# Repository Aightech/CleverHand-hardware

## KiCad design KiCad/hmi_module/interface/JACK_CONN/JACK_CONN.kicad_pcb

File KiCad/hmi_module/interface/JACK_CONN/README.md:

# Communication Module
This module is responsible for handling the communication between the different modules of the master node.

The communication bus is composed of :
- Power supply (3.3V) and ground
- SPI bus (POCI, PICO, SCK)
- I2C bus (SDA, SCL)
- Address bus (A0, A1, A2, A3, A4)
- External reference voltage (AREF)

When the module is connected to the bus, it is assigned an address by the master node. This address is used to identify the module on the bus.
The communication module will will activate the chip select line of the associated sensor module when the address bus matches its address.
Additionally, each module has a unique identifier that is used to identify the module on the I2C bus.

## Electrical Schematic

## PCB Layout

## 3D Model

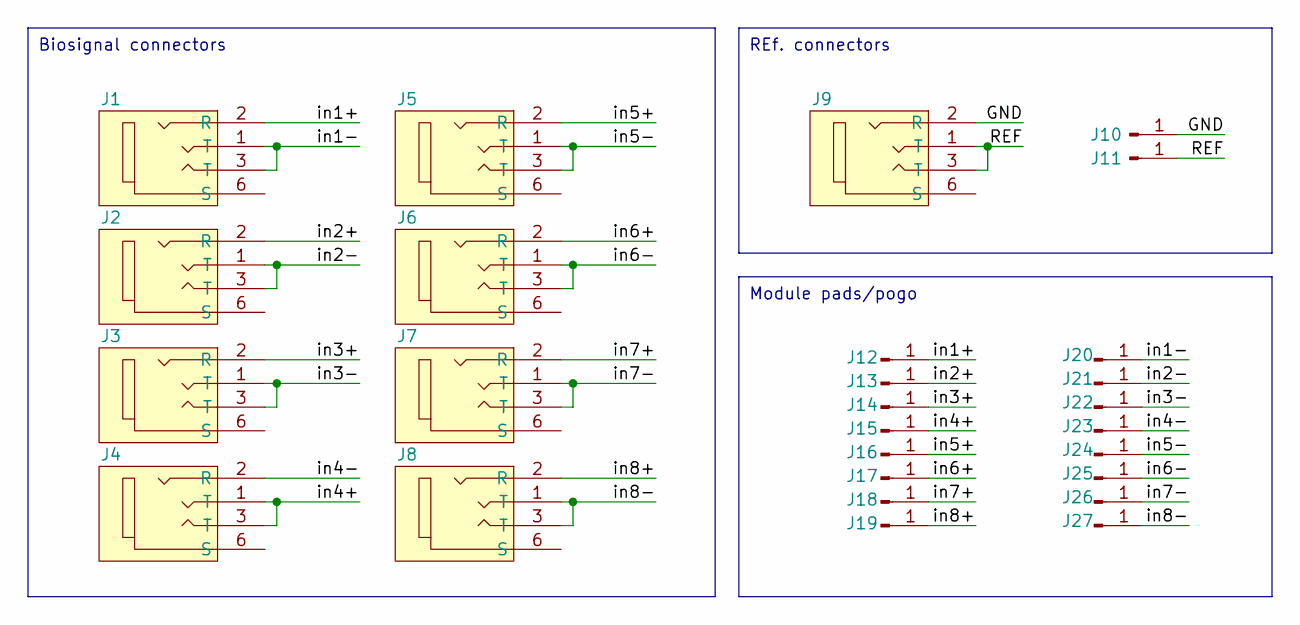
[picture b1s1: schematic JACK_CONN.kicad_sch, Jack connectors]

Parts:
J1, J2, J3, J4, J5, J6, J7, J8, J9: jack2.5_PJ-210B; Jack_Socket_PJ-210B
J10, J11: Conn_01x01_Pin; PinHeader_1x01_P2.54mm_Vertical
J12, J13, J14, J15, J16, J17, J18, J19, J20, J21, J22, J23, J24, J25, J26, J27: Conn_01x01_Pin; Pin_D1.2mm_pogo

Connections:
/GND: J9.2 (R), J10.1
/REF: J9.1 (T), J9.3 (T), J11.1
/in1+: J1.2 (R), J12.1
/in1-: J1.1 (T), J1.3 (T), J20.1
/in2+: J2.2 (R), J13.1
/in2-: J2.1 (T), J2.3 (T), J21.1
/in3+: J3.2 (R), J14.1
/in3-: J3.1 (T), J3.3 (T), J22.1
/in4+: J4.1 (T), J4.3 (T), J15.1
/in4-: J4.2 (R), J23.1
/in5+: J5.2 (R), J16.1
/in5-: J5.1 (T), J5.3 (T), J24.1
/in6+: J6.2 (R), J17.1
/in6-: J6.1 (T), J6.3 (T), J25.1
/in7+: J7.2 (R), J18.1
/in7-: J7.1 (T), J7.3 (T), J26.1
/in8+: J8.2 (R), J19.1
/in8-: J8.1 (T), J8.3 (T), J27.1

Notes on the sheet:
Module pads/pogo
Biosignal connectors
REf. connectors

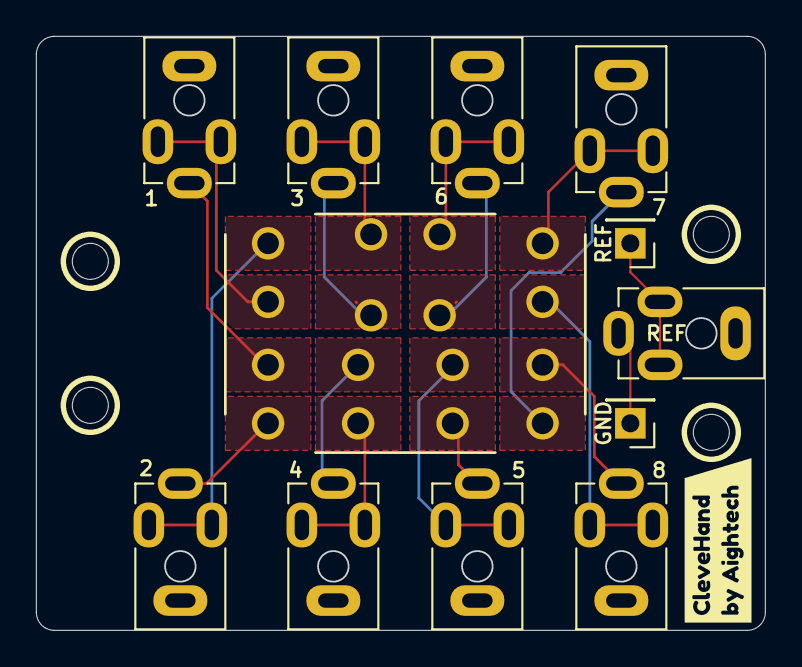
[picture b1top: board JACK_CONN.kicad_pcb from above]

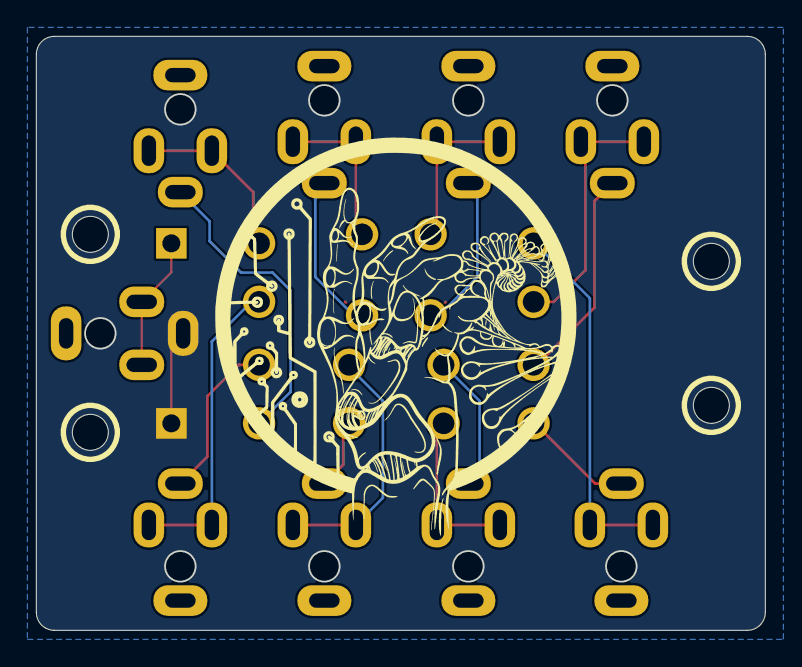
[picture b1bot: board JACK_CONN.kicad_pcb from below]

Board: 4 copper layers, 40.5 x 33.0 mm, 28 parts (16 on the bottom side), 18 nets.

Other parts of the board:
kibuzzard-6607178A: G***; kibuzzard-6607178A

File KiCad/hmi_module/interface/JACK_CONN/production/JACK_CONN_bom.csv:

"Reference","Value","Footprint","DNP","LCSC"
"J1","jack2.5_PJ-210B","00_custom-footprints:Jack_Socket_PJ-210B","",""
"J2","jack2.5_PJ-210B","00_custom-footprints:Jack_Socket_PJ-210B","",""
"J3","jack2.5_PJ-210B","00_custom-footprints:Jack_Socket_PJ-210B","",""
"J4","jack2.5_PJ-210B","00_custom-footprints:Jack_Socket_PJ-210B","",""
"J5","jack2.5_PJ-210B","00_custom-footprints:Jack_Socket_PJ-210B","",""
"J6","jack2.5_PJ-210B","00_custom-footprints:Jack_Socket_PJ-210B","",""
"J7","jack2.5_PJ-210B","00_custom-footprints:Jack_Socket_PJ-210B","",""
"J8","jack2.5_PJ-210B","00_custom-footprints:Jack_Socket_PJ-210B","",""
"J9","jack2.5_PJ-210B","00_custom-footprints:Jack_Socket_PJ-210B","",""
"J10","Conn_01x01_Pin","Connector_PinHeader_2.54mm:PinHeader_1x01_P2.54mm_Vertical","",""
"J11","Conn_01x01_Pin","Connector_PinHeader_2.54mm:PinHeader_1x01_P2.54mm_Vertical","",""
"J12","Conn_01x01_Pin","00_custom-footprints:Pin_D1.2mm_pogo","",""
"J13","Conn_01x01_Pin","00_custom-footprints:Pin_D1.2mm_pogo","",""
"J14","Conn_01x01_Pin","00_custom-footprints:Pin_D1.2mm_pogo","",""
"J15","Conn_01x01_Pin","00_custom-footprints:Pin_D1.2mm_pogo","",""
"J16","Conn_01x01_Pin","00_custom-footprints:Pin_D1.2mm_pogo","",""
"J17","Conn_01x01_Pin","00_custom-footprints:Pin_D1.2mm_pogo","",""
"J18","Conn_01x01_Pin","00_custom-footprints:Pin_D1.2mm_pogo","",""
"J19","Conn_01x01_Pin","00_custom-footprints:Pin_D1.2mm_pogo","",""
"J20","Conn_01x01_Pin","00_custom-footprints:Pin_D1.2mm_pogo","",""
"J21","Conn_01x01_Pin","00_custom-footprints:Pin_D1.2mm_pogo","",""
"J22","Conn_01x01_Pin","00_custom-footprints:Pin_D1.2mm_pogo","",""
"J23","Conn_01x01_Pin","00_custom-footprints:Pin_D1.2mm_pogo","",""
"J24","Conn_01x01_Pin","00_custom-footprints:Pin_D1.2mm_pogo","",""
"J25","Conn_01x01_Pin","00_custom-footprints:Pin_D1.2mm_pogo","",""
"J26","Conn_01x01_Pin","00_custom-footprints:Pin_D1.2mm_pogo","",""
"J27","Conn_01x01_Pin","00_custom-footprints:Pin_D1.2mm_pogo","",""

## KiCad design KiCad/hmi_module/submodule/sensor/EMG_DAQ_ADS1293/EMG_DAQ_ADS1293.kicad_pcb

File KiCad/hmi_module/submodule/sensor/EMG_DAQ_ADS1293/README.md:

# EMG ADS1293 Module
This module is a data acquisition module that embeds the ADS1293 analog front-end. It is responsible for acquiring the EMG signals from the electrodes.

## Electrical Schematic

## PCB Layout

## 3D Model

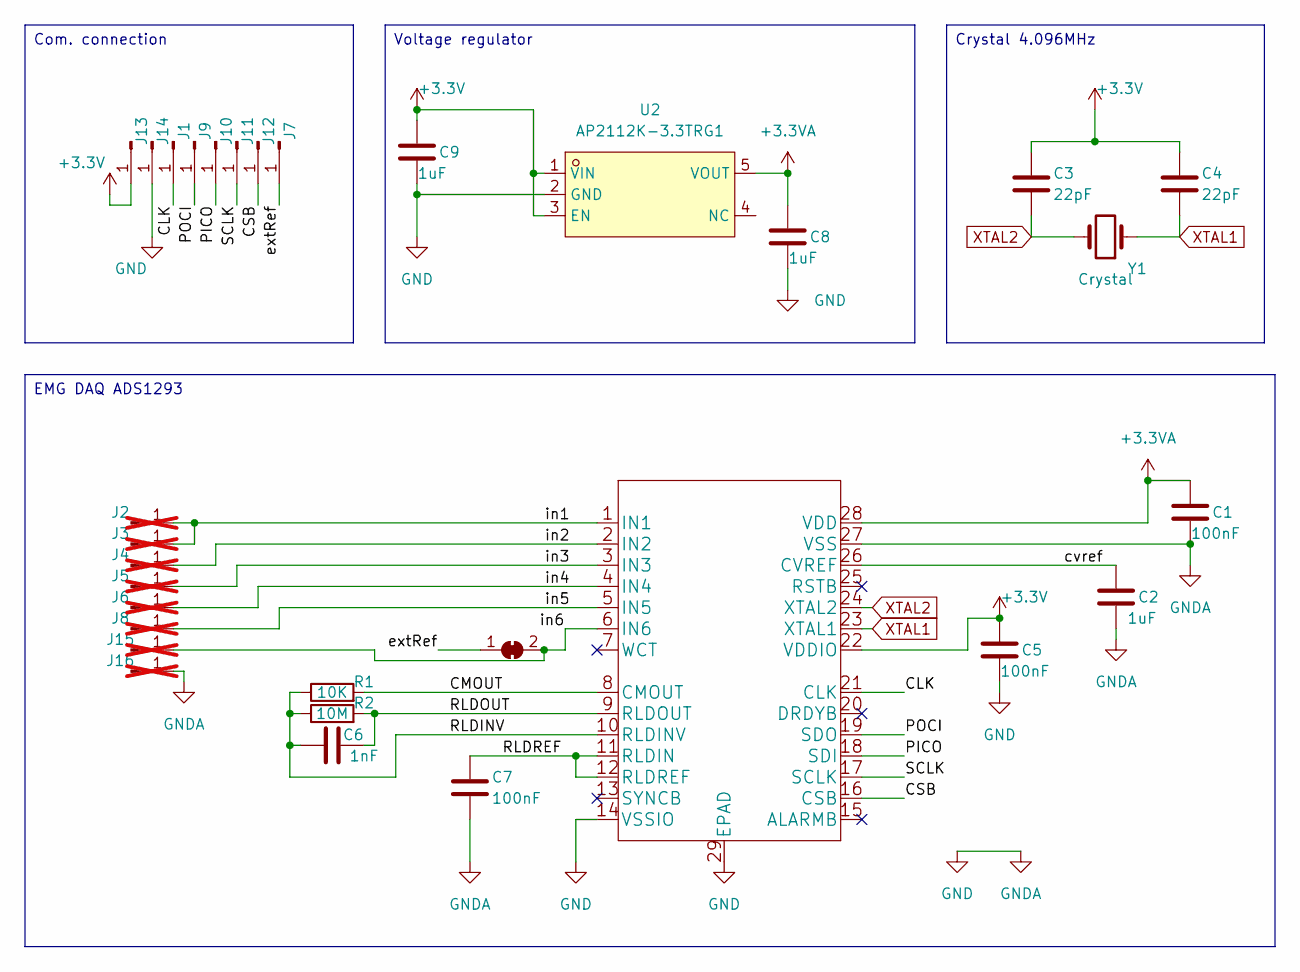
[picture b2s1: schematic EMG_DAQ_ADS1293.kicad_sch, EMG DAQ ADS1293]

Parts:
C1, C5, C7: 100nF; C_0402_1005Metric
C2, C8, C9: 1uF; C_0402_1005Metric
C3, C4: 22pF; C_0402_1005Metric
C6: 1nF; C_0402_1005Metric
J1, J7, J9, J10, J11, J12, J13, J14: Conn_01x01_Pin; PinHeader_1x01_P1.27mm_Vertical
J2, J3, J4, J5, J6, J8, J15, J16: Conn_01x01_Pin; PinHeader_1x01_P1.27mm_Vertical; not fitted
JP2: SolderJumper_2_Bridged; SolderJumper-2_P1.3mm_Bridged2Bar_RoundedPad1.0x1.5mm
R1: 10K; C_0402_1005Metric
R2: 10M; C_0402_1005Metric
U1: ADS1293CISQE-NOPB; ADS1293CISQE; LCSC C181260
U2: AP2112K-3.3TRG1; SOT-25-5_L2.9-W1.6-P0.95-LS2.8-BL; LCSC Part C51118
Y1: Crystal; Crystal_SMD_HC49-SD; LCSC C74858

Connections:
+3.3V: C3.1, C4.1, C5.1, C9.1, J13.1, U1.22 (VDDIO), U2.1 (VIN), U2.3 (EN)
+3.3VA: C1.1, C8.1, U1.28 (VDD), U2.5 (VOUT)
/CLK: J1.1, U1.21 (CLK)
/CMOUT: R1.2, U1.8 (CMOUT)
/CSB: J12.1, U1.16 (CSB)
/PICO: J10.1, U1.18 (SDI)
/POCI: J9.1, U1.19 (SDO)
/RLDINV: C6.1, R1.1, R2.1, U1.10 (RLDINV)
/RLDOUT: C6.2, R2.2, U1.9 (RLDOUT)
/RLDREF: C7.1, U1.11 (RLDIN), U1.12 (RLDREF)
/SCLK: J11.1, U1.17 (SCLK)
/cvref: C2.1, U1.26 (CVREF)
/extRef: J7.1, JP2.1 (A)
/in1: J2.1, J3.1, U1.1 (IN1)
/in2: J4.1, U1.2 (IN2)
/in3: J5.1, U1.3 (IN3)
/in4: J6.1, U1.4 (IN4)
/in5: J8.1, U1.5 (IN5)
/in6: J15.1, JP2.2 (B), U1.6 (IN6)
GND: C1.2, C2.2, C5.2, C7.2, C8.2, C9.2, J14.1, J16.1, U1.14 (VSSIO), U1.27 (VSS), U1.29 (EPAD), U2.2 (GND)
XTAL1: C4.2, U1.23 (XTAL1), Y1.1
XTAL2: C3.2, U1.24 (XTAL2), Y1.2

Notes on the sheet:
Com. connection
Crystal 4.096MHz
Voltage regulator
EMG DAQ ADS1293

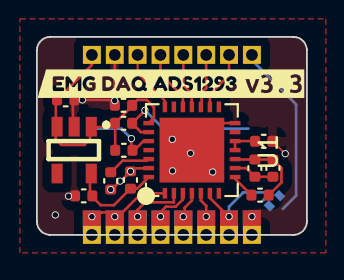
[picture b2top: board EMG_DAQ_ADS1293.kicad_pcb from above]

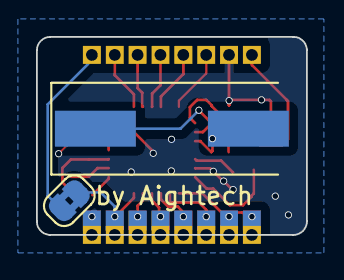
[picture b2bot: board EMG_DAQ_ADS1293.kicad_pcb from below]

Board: 4 copper layers, 15.0 x 11.0 mm, 33 parts (2 on the bottom side), 22 nets.

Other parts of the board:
kibuzzard-658D7E24: G***; kibuzzard-658D7E24
kibuzzard-69472C09: G***; kibuzzard-69472C09

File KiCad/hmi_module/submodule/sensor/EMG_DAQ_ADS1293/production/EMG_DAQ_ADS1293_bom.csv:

"Reference","Value","Footprint","DNP","LCSC"
"C1","100nF","Capacitor_SMD:C_0402_1005Metric","",""
"C2","1uF","Capacitor_SMD:C_0402_1005Metric","",""
"C3","22pF","Capacitor_SMD:C_0402_1005Metric","",""
"C4","22pF","Capacitor_SMD:C_0402_1005Metric","",""
"C5","100nF","Capacitor_SMD:C_0402_1005Metric","",""
"C6","1nF","Capacitor_SMD:C_0402_1005Metric","",""
"C7","100nF","Capacitor_SMD:C_0402_1005Metric","",""
"C8","1uF","Capacitor_SMD:C_0402_1005Metric","",""
"C9","1uF","Capacitor_SMD:C_0402_1005Metric","",""
"J1","Conn_01x01_Pin","Connector_PinHeader_1.27mm:PinHeader_1x01_P1.27mm_Vertical","",""
"J7","Conn_01x01_Pin","Connector_PinHeader_1.27mm:PinHeader_1x01_P1.27mm_Vertical","",""
"J9","Conn_01x01_Pin","Connector_PinHeader_1.27mm:PinHeader_1x01_P1.27mm_Vertical","",""
"J10","Conn_01x01_Pin","Connector_PinHeader_1.27mm:PinHeader_1x01_P1.27mm_Vertical","",""
"J11","Conn_01x01_Pin","Connector_PinHeader_1.27mm:PinHeader_1x01_P1.27mm_Vertical","",""
"J12","Conn_01x01_Pin","Connector_PinHeader_1.27mm:PinHeader_1x01_P1.27mm_Vertical","",""
"J13","Conn_01x01_Pin","Connector_PinHeader_1.27mm:PinHeader_1x01_P1.27mm_Vertical","",""
"J14","Conn_01x01_Pin","Connector_PinHeader_1.27mm:PinHeader_1x01_P1.27mm_Vertical","",""
"JP2","SolderJumper_2_Bridged","Jumper:SolderJumper-2_P1.3mm_Bridged2Bar_RoundedPad1.0x1.5mm","",""
"R1","10K","Capacitor_SMD:C_0402_1005Metric","",""
"R2","10M","Capacitor_SMD:C_0402_1005Metric","",""
"U1","ADS1293CISQE-NOPB","00_Custom:ADS1293CISQE","",""
"U2","AP2112K-3.3TRG1","00_lcsc:SOT-25-5_L2.9-W1.6-P0.95-LS2.8-BL","","C51118"
"Y1","Crystal","Crystal:Crystal_SMD_HC49-SD","",""

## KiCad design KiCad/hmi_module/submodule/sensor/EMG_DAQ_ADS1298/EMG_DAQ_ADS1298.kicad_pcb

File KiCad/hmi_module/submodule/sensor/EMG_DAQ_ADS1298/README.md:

# EMG ADS1298 Module
This module is a data acquisition module that embeds the ADS1298 analog front-end. It is responsible for acquiring the EMG signals from the electrodes.

## Electrical Schematic

## PCB Layout

## 3D Model

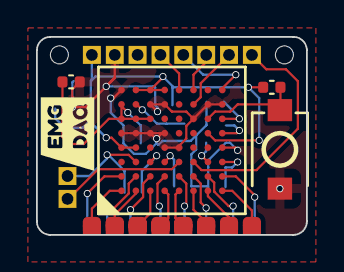
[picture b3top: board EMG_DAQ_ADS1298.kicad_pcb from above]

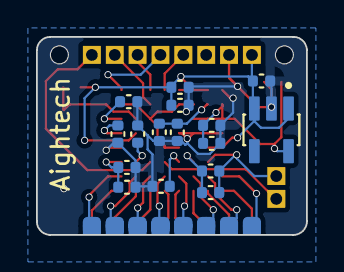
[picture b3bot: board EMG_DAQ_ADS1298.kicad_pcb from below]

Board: 4 copper layers, 15.0 x 11.0 mm, 47 parts (24 on the bottom side), 34 nets.

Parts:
C1, C2, C3, C5, C11, C12: 1uF; C_0402_1005Metric
C4, C6, C9, C14: 100nF; C_0402_1005Metric
C7: 1.5nF; C_0402_1005Metric
C8, C13: 10uF; C_0402_1005Metric
C10: 1nF; C_0402_1005Metric
C15: 22uF; C_0402_1005Metric
J1, J2, J3, J4, J5, J6, J7, J8, J25, J26: Conn_01x01_Pin; PinHeader_1x01_P1.27mm_Vertical
J9, J10, J11, J12, J13, J14, J15, J16, J17, J18, J19, J20, J21, J22, J23, J24: Conn_01x01_Pin; SolderWirePad_1x01_SMD_1x2mm
R1: 1M; C_0402_1005Metric
R2: 10K; C_0402_1005Metric
SW1: TS-1088R-02026; SW-SMD_L3.9-W3.0-P4.45
U1: AP2112K-3.3TRG1; SOT95P285X140-5N
U2: ADS1298CZXGT; NFBGA-64_L8.0-W8.0-R8-C8-P0.80-TL
kibuzzard-6569F40D: G***; kibuzzard-6569F40D

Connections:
+3.3V: C1.1, C3.2, C4.2, J1.1, R2.2, U1.1 (VIN), U1.3 (EN), U2.A4 (AVDD), U2.B4 (AVDD), U2.B8 (CLKSEL), U2.C8 (DVDD), U2.D8 (DVDD), U2.G5 (~PWDN)
+3.3VA: C2.1, C8.1, C9.1, U1.5 (VOUT), U2.A6 (AVDD), U2.A7 (AVDD1), U2.B6 (AVDD), U2.C6 (AVDD)
/BIAS_INV: C7.2, R1.1, U2.C3 (RLDINV)
/BIAS_OUT: C7.1, J26.1, R1.2, U2.B3 (RLDOUT)
/CSB: J7.1, U2.F7 (CS)
/PICO: J5.1, U2.H8 (DIN)
/POCI: J4.1, U2.E8 (DOUT)
/RESET: R2.1, SW1.1, U2.G6 (~RESET)
/Refp: J25.1, U2.E3 (TESTP_PACE_OUT1)
/SCLK: J6.1, U2.F8 (SCLK)
/VCAP1: C15.1, U2.H5 (VCAP1)
/VCAP2: C12.1, U2.H6 (VCAP2)
/VCAP3: C5.1, C6.1, U2.B7 (VCAP3)
/VCAP4: C11.1, U2.G3 (VCAP4)
/VREFP: C13.1, C14.1, U2.H3 (VREFP)
/WCT: C10.1, U2.D3 (WCT)
/extRef: J8.1, U2.F3 (TESTN_PACE_OUT2)
/in1+: J16.1, U2.H1 (IN1P)
/in1-: J24.1, U2.H2 (IN1N)
/in2+: J15.1, U2.G1 (IN2P)
/in2-: J23.1, U2.G2 (IN2N)
/in3+: J14.1, U2.F1 (IN3P)
/in3-: J22.1, U2.F2 (IN3N)
/in4+: J13.1, U2.E1 (IN4P)
/in4-: J21.1, U2.E2 (IN4N)
/in5+: J12.1, U2.D1 (IN5P)
/in5-: J20.1, U2.D2 (IN5N)
/in6+: J11.1, U2.C1 (IN6P)
/in6-: J19.1, U2.C2 (IN6N)
/in7+: J10.1, U2.B1 (IN7P)
/in7-: J18.1, U2.B2 (IN7N)
/in8+: J9.1, U2.A1 (IN8P)
/in8-: J17.1, U2.A2 (IN8N)
GND: C1.2, C2.2, C3.1, C4.1, C5.2, C6.2, C8.2, C9.2, C10.2, C11.2, C12.2, C13.2, C14.2, C15.2, J2.1, SW1.2, U1.2 (GND), U2.A5 (AVSS), U2.A8 (AVSS1), U2.B5 (AVSS), U2.C5 (AVSS), U2.C7 (DGND), U2.D4 (AVSS), U2.D5 (AVSS), U2.D7 (DGND), U2.E4 (RESV1), U2.F6 (DAISY_IN), U2.G7 (START), U2.H4 (VREFN), U2.H7 (DGND)

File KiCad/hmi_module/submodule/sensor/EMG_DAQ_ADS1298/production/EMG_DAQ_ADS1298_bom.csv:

"Reference","Value","Footprint","DNP","LCSC"
"C1","1uF","Capacitor_SMD:C_0402_1005Metric","",""
"C2","1uF","Capacitor_SMD:C_0402_1005Metric","",""
"C3","1uF","Capacitor_SMD:C_0402_1005Metric","",""
"C4","100nF","Capacitor_SMD:C_0402_1005Metric","",""
"C5","1uF","Capacitor_SMD:C_0402_1005Metric","",""
"C6","100nF","Capacitor_SMD:C_0402_1005Metric","",""
"C7","1.5nF","Capacitor_SMD:C_0402_1005Metric","",""
"C8","10uF","Capacitor_SMD:C_0402_1005Metric","",""
"C9","100nF","Capacitor_SMD:C_0402_1005Metric","",""
"C10","1nF","Capacitor_SMD:C_0402_1005Metric","",""
"C11","1uF","Capacitor_SMD:C_0402_1005Metric","",""
"C12","1uF","Capacitor_SMD:C_0402_1005Metric","",""
"C13","10uF","Capacitor_SMD:C_0402_1005Metric","",""
"C14","100nF","Capacitor_SMD:C_0402_1005Metric","",""
"C15","22uF","Capacitor_SMD:C_0402_1005Metric","",""
"J1","Conn_01x01_Pin","00_custom-footprints:PinHeader_1x01_P1.27mm_Vertical","",""
"J2","Conn_01x01_Pin","00_custom-footprints:PinHeader_1x01_P1.27mm_Vertical","",""
"J3","Conn_01x01_Pin","00_custom-footprints:PinHeader_1x01_P1.27mm_Vertical","",""
"J4","Conn_01x01_Pin","00_custom-footprints:PinHeader_1x01_P1.27mm_Vertical","",""
"J5","Conn_01x01_Pin","00_custom-footprints:PinHeader_1x01_P1.27mm_Vertical","",""
"J6","Conn_01x01_Pin","00_custom-footprints:PinHeader_1x01_P1.27mm_Vertical","",""
"J7","Conn_01x01_Pin","00_custom-footprints:PinHeader_1x01_P1.27mm_Vertical","",""
"J8","Conn_01x01_Pin","00_custom-footprints:PinHeader_1x01_P1.27mm_Vertical","",""
"J9","Conn_01x01_Pin","00_custom-footprints:SolderWirePad_1x01_SMD_1x2mm","",""
"J10","Conn_01x01_Pin","00_custom-footprints:SolderWirePad_1x01_SMD_1x2mm","",""
"J11","Conn_01x01_Pin","00_custom-footprints:SolderWirePad_1x01_SMD_1x2mm","",""
"J12","Conn_01x01_Pin","00_custom-footprints:SolderWirePad_1x01_SMD_1x2mm","",""
"J13","Conn_01x01_Pin","00_custom-footprints:SolderWirePad_1x01_SMD_1x2mm","",""
"J14","Conn_01x01_Pin","00_custom-footprints:SolderWirePad_1x01_SMD_1x2mm","",""
"J15","Conn_01x01_Pin","00_custom-footprints:SolderWirePad_1x01_SMD_1x2mm","",""
"J16","Conn_01x01_Pin","00_custom-footprints:SolderWirePad_1x01_SMD_1x2mm","",""
"J17","Conn_01x01_Pin","00_custom-footprints:SolderWirePad_1x01_SMD_1x2mm","",""
"J18","Conn_01x01_Pin","00_custom-footprints:SolderWirePad_1x01_SMD_1x2mm","",""
"J19","Conn_01x01_Pin","00_custom-footprints:SolderWirePad_1x01_SMD_1x2mm","",""
"J20","Conn_01x01_Pin","00_custom-footprints:SolderWirePad_1x01_SMD_1x2mm","",""
"J21","Conn_01x01_Pin","00_custom-footprints:SolderWirePad_1x01_SMD_1x2mm","",""
"J22","Conn_01x01_Pin","00_custom-footprints:SolderWirePad_1x01_SMD_1x2mm","",""
"J23","Conn_01x01_Pin","00_custom-footprints:SolderWirePad_1x01_SMD_1x2mm","",""
"J24","Conn_01x01_Pin","00_custom-footprints:SolderWirePad_1x01_SMD_1x2mm","",""
"J25","Conn_01x01_Pin","00_custom-footprints:PinHeader_1x01_P1.27mm_Vertical","",""
"J26","Conn_01x01_Pin","00_custom-footprints:PinHeader_1x01_P1.27mm_Vertical","",""
"R1","1M","Capacitor_SMD:C_0402_1005Metric","",""
"R2","10K","Capacitor_SMD:C_0402_1005Metric","",""
"SW1","TS-1088R-02026","00_lcsc:SW-SMD_L3.9-W3.0-P4.45","","C455280"
"U1","AP2112K-3.3TRG1","00_custom-footprints:SOT95P285X140-5N","",""
"U2","ADS1298CZXGT","00_lcsc:NFBGA-64_L8.0-W8.0-R8-C8-P0.80-TL","","C882732"

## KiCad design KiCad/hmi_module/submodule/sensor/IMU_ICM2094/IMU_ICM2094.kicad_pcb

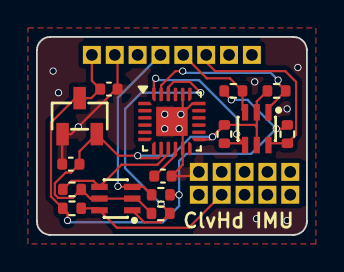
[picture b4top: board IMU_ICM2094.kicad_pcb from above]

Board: 4 copper layers, 15.0 x 11.0 mm, 34 parts (1 on the bottom side), 12 nets.

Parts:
C1, C2: 1uF; C_0402_1005Metric
C5: 100nF; C_0402_1005Metric
J1, J2, J3, J4, J5, J6, J7, J8, J9, J10, J11, J12, J13, J14, J15, J16, J17, J18: Conn_01x01_Pin; PinHeader_1x01_P1.27mm_Vertical
R1, R2, R3, R4, R5, R6, R7, R8: 4.7k; R_0402_1005Metric
U1: MCP1700T-1802E/TT; SOT-23-3_L2.9-W1.3-P1.90-LS2.4-BR
U3, U5: BSS138BKS; SOT-363_L2.1-W1.3-P0.65-LS2.3-BL
U4: ICM-20948; QFN-24-1EP_3x3mm_P0.4mm_EP1.75x1.6mm
kibuzzard-66093797: G***; kibuzzard-66093797

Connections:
+3.3V: C1.1, J1.1, R1.1, R4.1, R5.1, R8.1, U1.3 (VIN)
/1.8V: C2.1, R2.2, R3.1, R6.2, R7.1, U1.2 (VOUT), U3.2 (G2), U3.5 (G1), U4.8 (VDDIO), U4.13 (VDD), U5.2 (G2), U5.5 (G1)
/CSB: J17.1, R8.2, U5.6 (D2)
/CS_1.8V: R7.2, U4.22 (nCS), U5.1 (S2)
/PICO: J5.1, R1.2, U3.3 (D1)
/PICO_1.8V: R2.1, U3.4 (S1), U4.24 (SDA/SDI)
/POCI: J4.1, R5.2, U5.3 (D1)
/POCI_1.8V: R6.1, U4.9 (SDO/AD0), U5.4 (S1)
/SCK_1.8V: R3.2, U3.1 (S2), U4.23 (SCL/SCLK)
/SCLK: J6.1, R4.2, U3.6 (D2)
GND: C1.2, C2.2, C5.2, J2.1, J18.1, U1.1 (GND), U4.11 (FSYNC), U4.18 (GND), U4.20 (RESV), U4.25 (EP)
unnamed: C5.1, U4.10 (REGOUT)

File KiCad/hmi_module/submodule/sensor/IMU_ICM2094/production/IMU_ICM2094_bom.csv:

"Reference","Value","Footprint","DNP","LCSC"
"C1","1uF","Capacitor_SMD:C_0402_1005Metric","",""
"C2","1uF","Capacitor_SMD:C_0402_1005Metric","",""
"C5","100nF","Capacitor_SMD:C_0402_1005Metric","",""
"J1","Conn_01x01_Pin","00_custom-footprints:PinHeader_1x01_P1.27mm_Vertical","",""
"J2","Conn_01x01_Pin","00_custom-footprints:PinHeader_1x01_P1.27mm_Vertical","",""
"J3","Conn_01x01_Pin","00_custom-footprints:PinHeader_1x01_P1.27mm_Vertical","",""
"J4","Conn_01x01_Pin","00_custom-footprints:PinHeader_1x01_P1.27mm_Vertical","",""
"J5","Conn_01x01_Pin","00_custom-footprints:PinHeader_1x01_P1.27mm_Vertical","",""
"J6","Conn_01x01_Pin","00_custom-footprints:PinHeader_1x01_P1.27mm_Vertical","",""
"J7","Conn_01x01_Pin","00_custom-footprints:PinHeader_1x01_P1.27mm_Vertical","",""
"J8","Conn_01x01_Pin","00_custom-footprints:PinHeader_1x01_P1.27mm_Vertical","",""
"J9","Conn_01x01_Pin","00_custom-footprints:PinHeader_1x01_P1.27mm_Vertical","",""
"J10","Conn_01x01_Pin","00_custom-footprints:PinHeader_1x01_P1.27mm_Vertical","",""
"J11","Conn_01x01_Pin","00_custom-footprints:PinHeader_1x01_P1.27mm_Vertical","",""
"J12","Conn_01x01_Pin","00_custom-footprints:PinHeader_1x01_P1.27mm_Vertical","",""
"J13","Conn_01x01_Pin","00_custom-footprints:PinHeader_1x01_P1.27mm_Vertical","",""
"J14","Conn_01x01_Pin","00_custom-footprints:PinHeader_1x01_P1.27mm_Vertical","",""
"J15","Conn_01x01_Pin","00_custom-footprints:PinHeader_1x01_P1.27mm_Vertical","",""
"J16","Conn_01x01_Pin","00_custom-footprints:PinHeader_1x01_P1.27mm_Vertical","",""
"J17","Conn_01x01_Pin","00_custom-footprints:PinHeader_1x01_P1.27mm_Vertical","",""
"J18","Conn_01x01_Pin","00_custom-footprints:PinHeader_1x01_P1.27mm_Vertical","",""
"R1","4.7k","Resistor_SMD:R_0402_1005Metric","",""
"R2","4.7k","Resistor_SMD:R_0402_1005Metric","",""
"R3","4.7k","Resistor_SMD:R_0402_1005Metric","",""
"R4","4.7k","Resistor_SMD:R_0402_1005Metric","",""
"R5","4.7k","Resistor_SMD:R_0402_1005Metric","",""
"R6","4.7k","Resistor_SMD:R_0402_1005Metric","",""
"R7","4.7k","Resistor_SMD:R_0402_1005Metric","",""
"R8","4.7k","Resistor_SMD:R_0402_1005Metric","",""
"U1","MCP1700T-1802E/TT","00_lcsc:SOT-23-3_L2.9-W1.3-P1.90-LS2.4-BR","","C150796"
"U3","BSS138BKS","00_lcsc:SOT-363_L2.1-W1.3-P0.65-LS2.3-BL","","C5224290"
"U4","ICM-20948","Package_DFN_QFN:QFN-24-1EP_3x3mm_P0.4mm_EP1.75x1.6mm","","C726001"
"U5","BSS138BKS","00_lcsc:SOT-363_L2.1-W1.3-P0.65-LS2.3-BL","","C5224290"

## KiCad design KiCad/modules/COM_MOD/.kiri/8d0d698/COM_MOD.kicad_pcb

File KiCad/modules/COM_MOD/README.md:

# Communication Module
This module is responsible for handling the communication between the different modules of the controller node.

The communication bus is composed of :
- Power supply (3.3V) and ground
- SPI bus (MISO, MOSI, SCK)
- I2C bus (SDA, SCL)
- Address bus (A0, A1, A2, A3, A4)
- External reference voltage (AREF)

When the module is connected to the bus, it is assigned an address by the controller node. This address is used to identify the module on the bus.
The communication module will activate the chip select line of the associated sensor module when the address bus matches its address.
Additionally, each module has a unique identifier that is used to identify the module on the I2C bus.

## Electrical Schematic

## PCB Layout

## 3D Model

```stl
// COM_MOD_pcb.stl

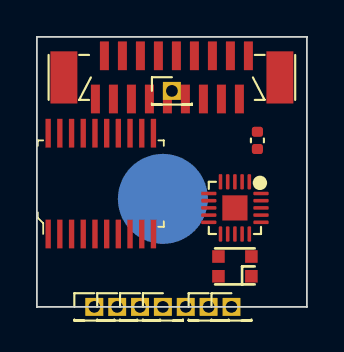
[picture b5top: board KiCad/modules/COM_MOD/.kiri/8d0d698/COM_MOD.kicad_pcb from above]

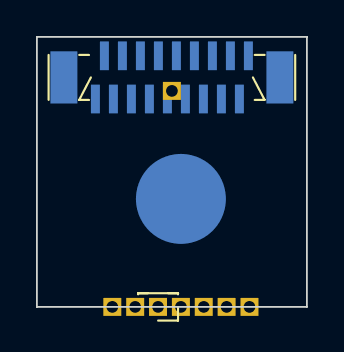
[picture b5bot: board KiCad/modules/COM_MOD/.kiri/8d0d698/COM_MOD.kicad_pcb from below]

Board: 2 copper layers, 15.0 x 15.0 mm, 14 parts (2 on the bottom side), 3 nets, no tracks yet.

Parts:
C1: 4.7uF; C_0402_1005Metric
J1, J2, J3, J5, J6, J7, J8, J9: Conn_01x01_Pin; PinHeader_1x01_P1.27mm_Vertical
J4, J10: XF2J-1824-12A
LED1: WS2812-2020
U1: HC32L110C6UA; QFN-20-1EP_3x3mm_P0.4mm_EP1.4x1.4mm
U2: 74HC688; TSSOP-20_W4.4mm

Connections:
+3.3V: LED1.4 (VDD), U1.6 (AVCC)
/Vcap: C1.2, U1.5 (Vcap)
GND: C1.1, LED1.2 (GND), U1.4 (GND), U1.21 (GPIO)

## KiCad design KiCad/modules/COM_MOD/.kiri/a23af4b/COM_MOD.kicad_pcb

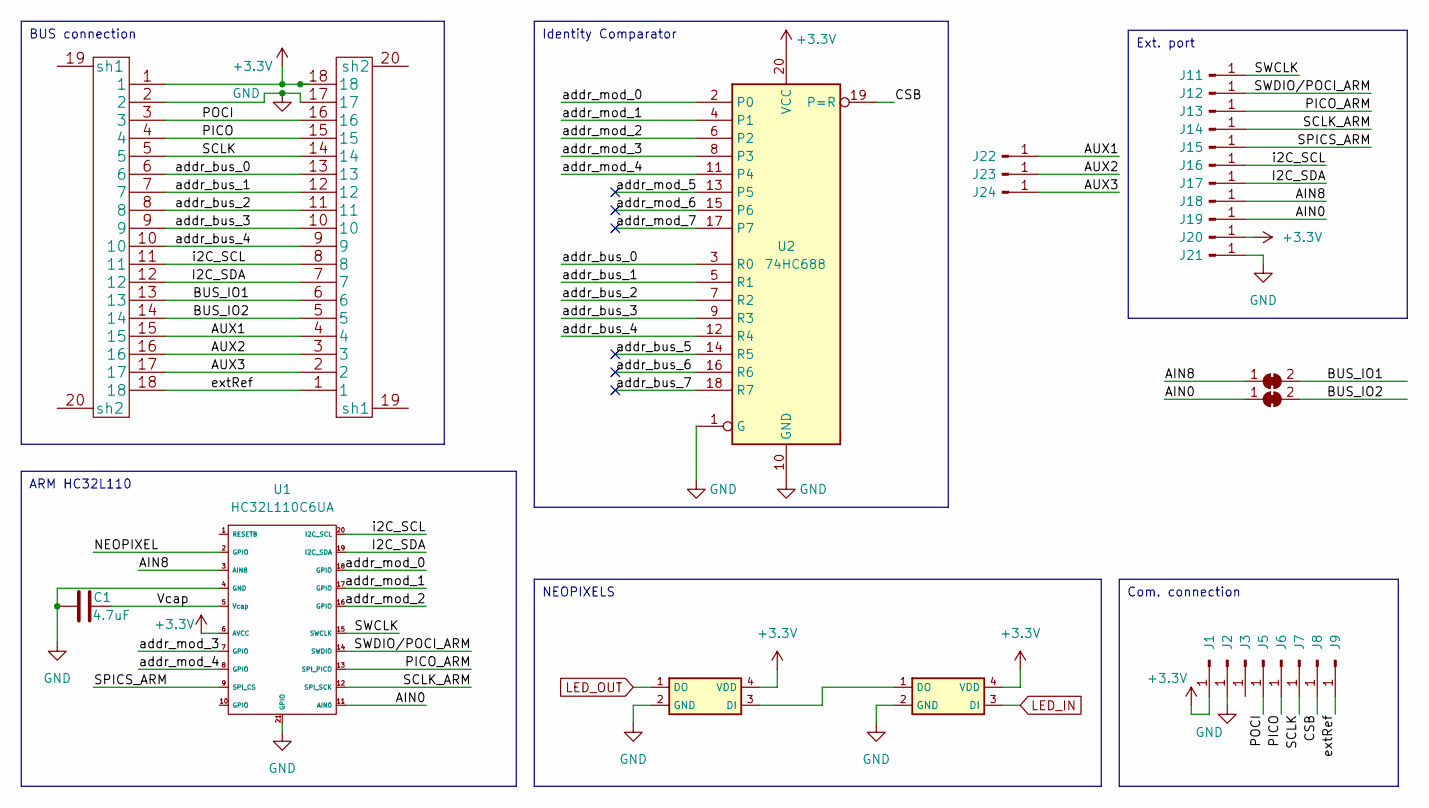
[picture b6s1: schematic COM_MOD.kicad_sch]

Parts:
C1: 4.7uF; C_0402_1005Metric
J1, J2, J3, J5, J6, J7, J8, J9, J11, J12, J13, J14, J15, J16, J17, J18, J19, J20, J21, J22, J23, J24: Conn_01x01_Pin; PinHeader_1x01_P1.27mm_Vertical
J4, J10: XF2J-1824-12A; XUNPU_FPC_05F_18P_H20
JP1, JP2: SolderJumper_2_Bridged; SolderJumper-2_P1.3mm_Bridged_RoundedPad1.0x1.5mm
LED1, LED2: WS2812-2020
U1: HC32L110C6UA; QFN-20-1EP_3x3mm_P0.4mm_EP1.4x1.4mm
U2: 74HC688; TSSOP-20_W4.4mm

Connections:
+3.3V: J1.1, J4.1, J10.18, J20.1, LED1.4 (VDD), LED2.4 (VDD), U1.6 (AVCC), U2.20 (VCC)
/AIN0: J19.1, JP2.1 (A), U1.11 (AIN0)
/AIN8: J18.1, JP1.1 (A), U1.3 (AIN8)
/AUX1: J4.15, J10.4, J22.1
/AUX2: J4.16, J10.3, J23.1
/AUX3: J4.17, J10.2, J24.1
/BUS_IO1: J4.13, J10.6, JP1.2 (B)
/BUS_IO2: J4.14, J10.5, JP2.2 (B)
/CSB: J8.1, U2.19 (P=R)
/I2C_SDA: J4.12, J10.7, J17.1, U1.19 (I2C_SDA)
/NEOPIXEL: U1.2 (GPIO)
/PICO: J4.4, J6.1, J10.15
/PICO_ARM: J13.1, U1.13 (SPI_PICO)
/POCI: J4.3, J5.1, J10.16
/SCLK: J4.5, J7.1, J10.14
/SCLK_ARM: J14.1, U1.12 (SPI_SCK)
/SPICS_ARM: J15.1, U1.9 (SPI_CS)
/SWCLK: J11.1, U1.15 (SWCLK)
/SWDIO/POCI_ARM: J12.1, U1.14 (SWDIO)
/Vcap: C1.2, U1.5 (Vcap)
/addr_bus_0: J4.6, J10.13, U2.3 (R0)
/addr_bus_1: J4.7, J10.12, U2.5 (R1)
/addr_bus_2: J4.8, J10.11, U2.7 (R2)
/addr_bus_3: J4.9, J10.10, U2.9 (R3)
/addr_bus_4: J4.10, J10.9, U2.12 (R4)
/addr_bus_5: U2.14 (R5)
/addr_bus_6: U2.16 (R6)
/addr_bus_7: U2.18 (R7)
/addr_mod_0: U1.18 (GPIO), U2.2 (P0)
/addr_mod_1: U1.17 (GPIO), U2.4 (P1)
/addr_mod_2: U1.16 (GPIO), U2.6 (P2)
/addr_mod_3: U1.7 (GPIO), U2.8 (P3)
/addr_mod_4: U1.8 (GPIO), U2.11 (P4)
/addr_mod_5: U2.13 (P5)
/addr_mod_6: U2.15 (P6)
/addr_mod_7: U2.17 (P7)
/extRef: J4.18, J9.1, J10.1
/i2C_SCL: J4.11, J10.8, J16.1, U1.20 (I2C_SCL)
GND: C1.1, J2.1, J4.2, J10.17, J21.1, LED1.2 (GND), LED2.2 (GND), U1.4 (GND), U1.21 (GPIO), U2.1 (G), U2.10 (GND)
LED_IN: LED1.3 (DI)
LED_OUT: LED2.1 (DO)
unnamed: LED1.1 (DO), LED2.3 (DI)

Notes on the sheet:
ARM HC32L110
NEOPIXELS
Identity Comparator
Com. connection
BUS connection
Ext. port

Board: 4 copper layers, 32 parts (3 on the bottom side), 33 nets, no tracks yet.

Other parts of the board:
kibuzzard-6569F493: G***; kibuzzard-6569F493

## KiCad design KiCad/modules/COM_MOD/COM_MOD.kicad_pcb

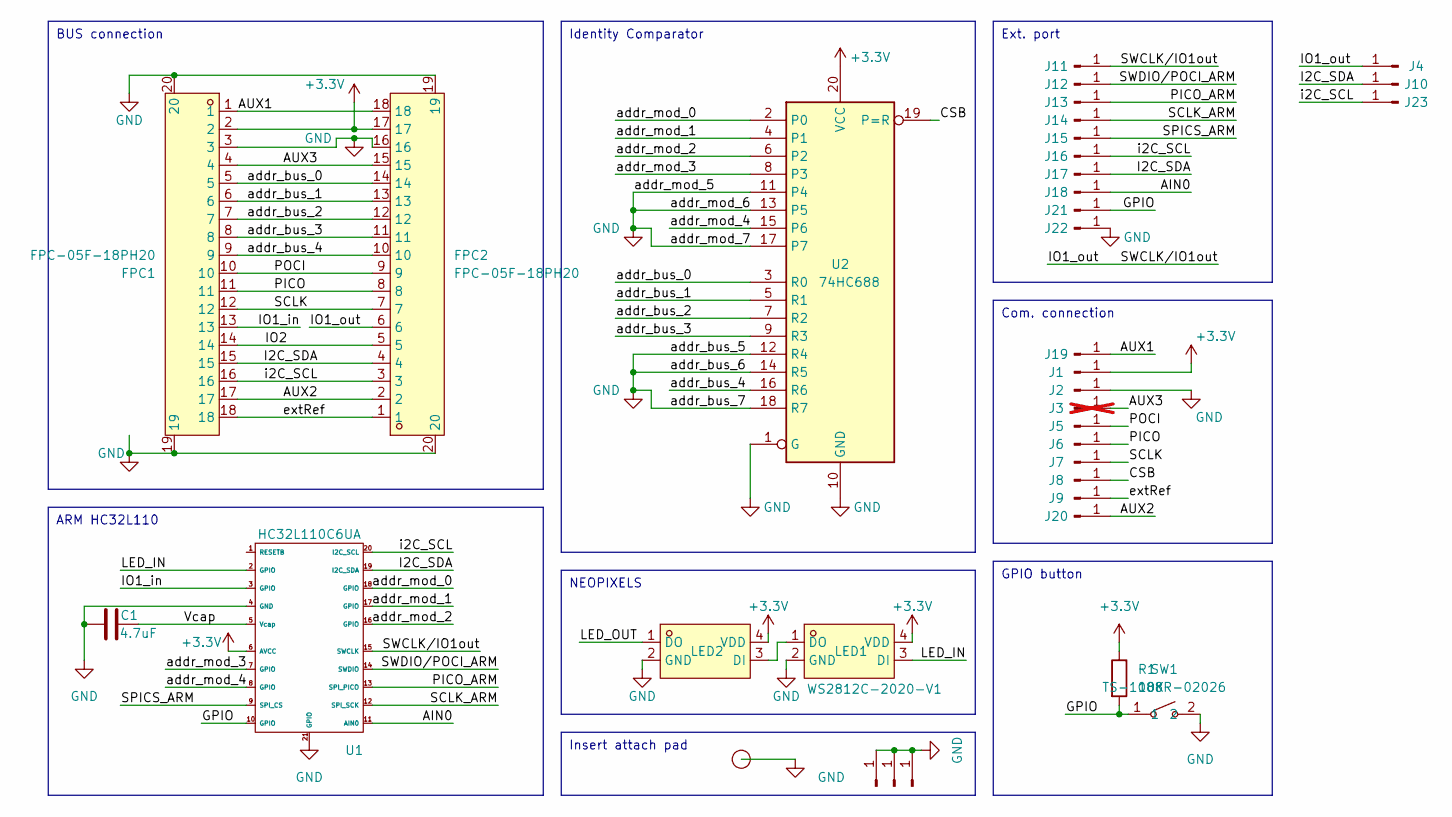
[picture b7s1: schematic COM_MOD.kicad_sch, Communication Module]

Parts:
C1: 4.7uF; C_0402_1005Metric; LCSC C23733
FPC1, FPC2: FPC-05F-18PH20; FPC-SMD_18P-P0.50_FPC-05F-18PH20; LCSC Part C2856802
I1: smd_insert; insert_1.2mm
J1, J2, J4, J5, J6, J7, J8, J9, J10, J11, J12, J13, J14, J15, J16, J17, J18, J19, J20, J21, J22, J23: Conn_01x01_Pin; PinHeader_1x01_P1.27mm_Vertical
J3: Conn_01x01_Pin; PinHeader_1x01_P1.27mm_Vertical; not fitted
J24, J25, J26: Conn_01x01_Pin; PinSocket_1x01_P2.54mm_Vertical
LED1: WS2812C-2020-V1; LED-SMD_4P-L2.0-W2.0-TL_WS2812B-2020; LCSC Part C2976072
LED2: WS2812C; LED-SMD_4P-L2.0-W2.0-TL_WS2812B-2020; LCSC Part C2976072
R1: 10K; R_0402_1005Metric; LCSC C25744
SW1: TS-1088R-02026; SW-SMD_L3.9-W3.0-P4.45; LCSC Part C455280
U1: HC32L110C6UA; QFN-20-1EP_3x3mm_P0.4mm_EP1.4x1.4mm; LCSC C493490
U2: 74HC688; TSSOP-20_W4.4mm; LCSC C132045

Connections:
+3.3V: FPC1.2, FPC2.17, J1.1, LED1.4 (VDD), LED2.4 (VDD), R1.1, U1.6 (AVCC), U2.20 (VCC)
/AIN0: J18.1, U1.11 (AIN0)
/AUX1: FPC1.1, FPC2.18, J19.1
/AUX2: FPC1.17, FPC2.2, J20.1
/AUX3: FPC1.4, FPC2.15, J3.1
/CSB: J8.1, U2.19 (P=R)
/GPIO: J21.1, R1.2, SW1.1, U1.10 (GPIO)
/I2C_SDA: FPC1.15, FPC2.4, J10.1, J17.1, U1.19 (I2C_SDA)
/IO1_in: FPC1.13, U1.3 (GPIO)
/IO1_out: FPC2.6, J4.1, J11.1, U1.15 (SWCLK)
/IO2: FPC1.14, FPC2.5
/LED_IN: LED1.3 (DI), U1.2 (GPIO)
/LED_OUT: LED2.1 (DO)
/PICO: FPC1.11, FPC2.8, J6.1
/PICO_ARM: J13.1, U1.13 (SPI_PICO)
/POCI: FPC1.10, FPC2.9, J5.1
/SCLK: FPC1.12, FPC2.7, J7.1
/SCLK_ARM: J14.1, U1.12 (SPI_SCK)
/SPICS_ARM: J15.1, U1.9 (SPI_CS)
/SWDIO/POCI_ARM: J12.1, U1.14 (SWDIO)
/Vcap: C1.2, U1.5 (Vcap)
/addr_bus_0: FPC1.5, FPC2.14, U2.3 (R0)
/addr_bus_1: FPC1.6, FPC2.13, U2.5 (R1)
/addr_bus_2: FPC1.7, FPC2.12, U2.7 (R2)
/addr_bus_3: FPC1.8, FPC2.11, U2.9 (R3)
/addr_bus_4: FPC1.9, FPC2.10, U2.16 (R6)
/addr_mod_0: U1.18 (GPIO), U2.2 (P0)
/addr_mod_1: U1.17 (GPIO), U2.4 (P1)
/addr_mod_2: U1.16 (GPIO), U2.6 (P2)
/addr_mod_3: U1.7 (GPIO), U2.8 (P3)
/addr_mod_4: U1.8 (GPIO), U2.15 (P6)
/extRef: FPC1.18, FPC2.1, J9.1
/i2C_SCL: FPC1.16, FPC2.3, J16.1, J23.1, U1.20 (I2C_SCL)
GND: C1.1, FPC1.3, FPC1.19, FPC1.20, FPC2.16, FPC2.19, FPC2.20, I1.1 (conn), J2.1, J22.1, J24.1, J25.1, J26.1, LED1.2 (GND), LED2.2 (GND), SW1.2, U1.4 (GND), U1.21 (GPIO), U2.1 (G), U2.10 (GND), U2.11 (P4), U2.12 (R4), U2.13 (P5), U2.14 (R5), U2.17 (P7), U2.18 (R7)
unnamed: LED1.1 (DO), LED2.3 (DI)

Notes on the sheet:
ARM HC32L110
Insert attach pad
NEOPIXELS
Identity Comparator
Com. connection
GPIO button
BUS connection
Ext. port

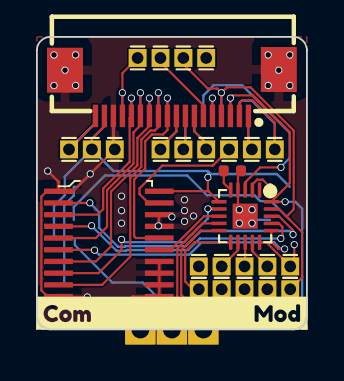
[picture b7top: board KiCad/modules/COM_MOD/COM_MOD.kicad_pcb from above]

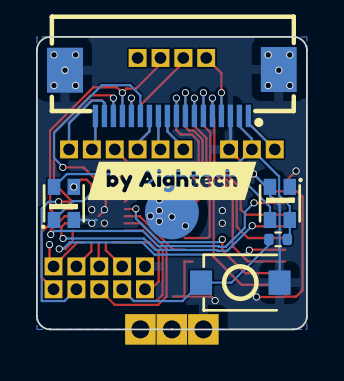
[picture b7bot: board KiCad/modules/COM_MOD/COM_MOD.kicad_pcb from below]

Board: 4 copper layers, 15.0 x 16.3 mm, 38 parts (7 on the bottom side), 34 nets.

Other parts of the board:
kibuzzard-658C3FF8: G***; kibuzzard-658C3FF8
kibuzzard-658C2757: G***; kibuzzard-658C2757
